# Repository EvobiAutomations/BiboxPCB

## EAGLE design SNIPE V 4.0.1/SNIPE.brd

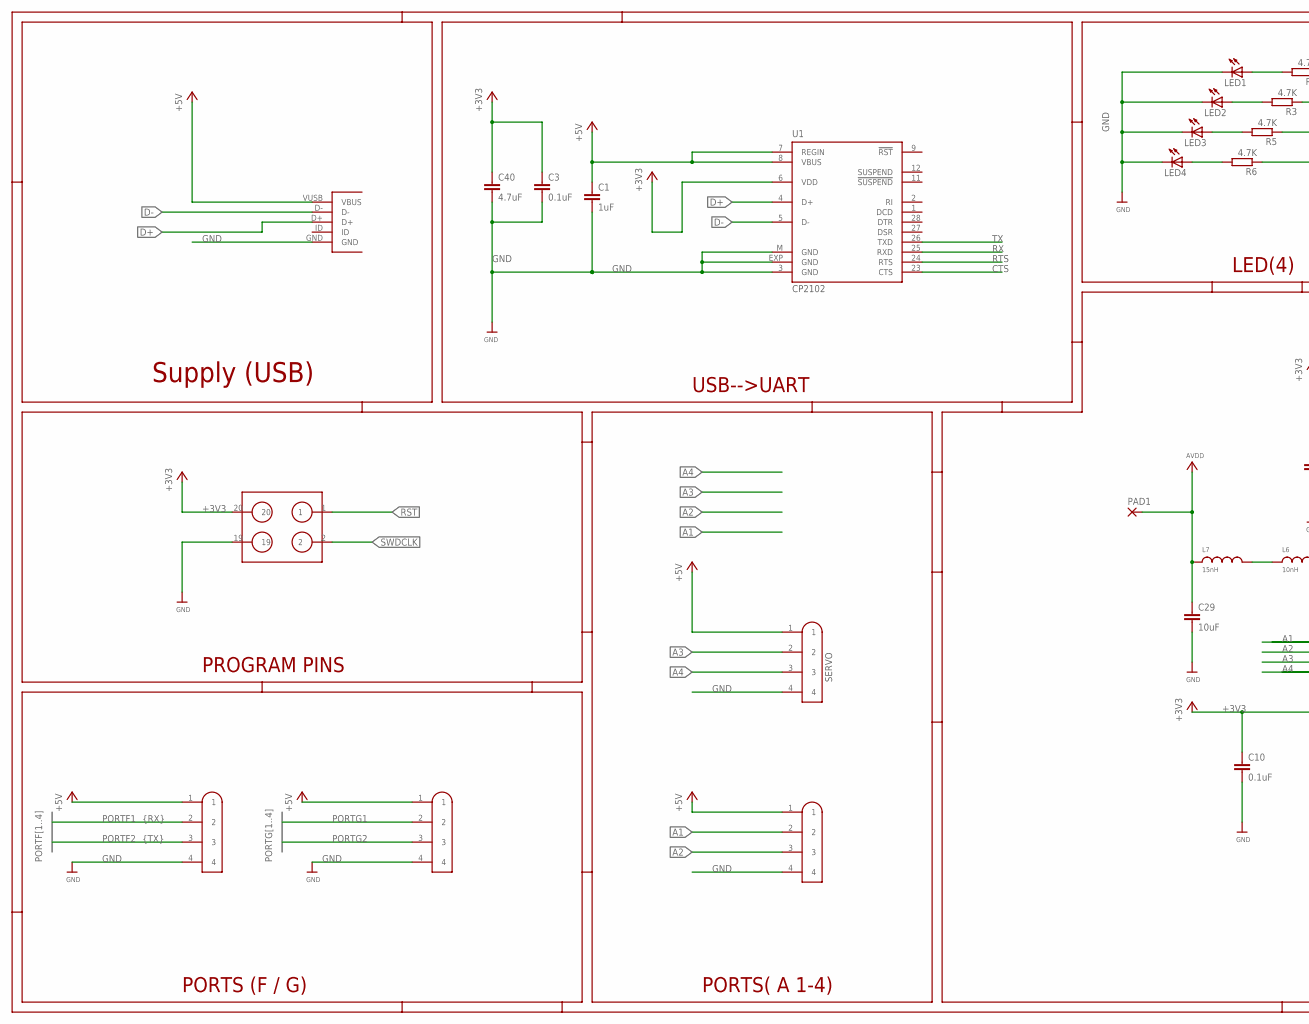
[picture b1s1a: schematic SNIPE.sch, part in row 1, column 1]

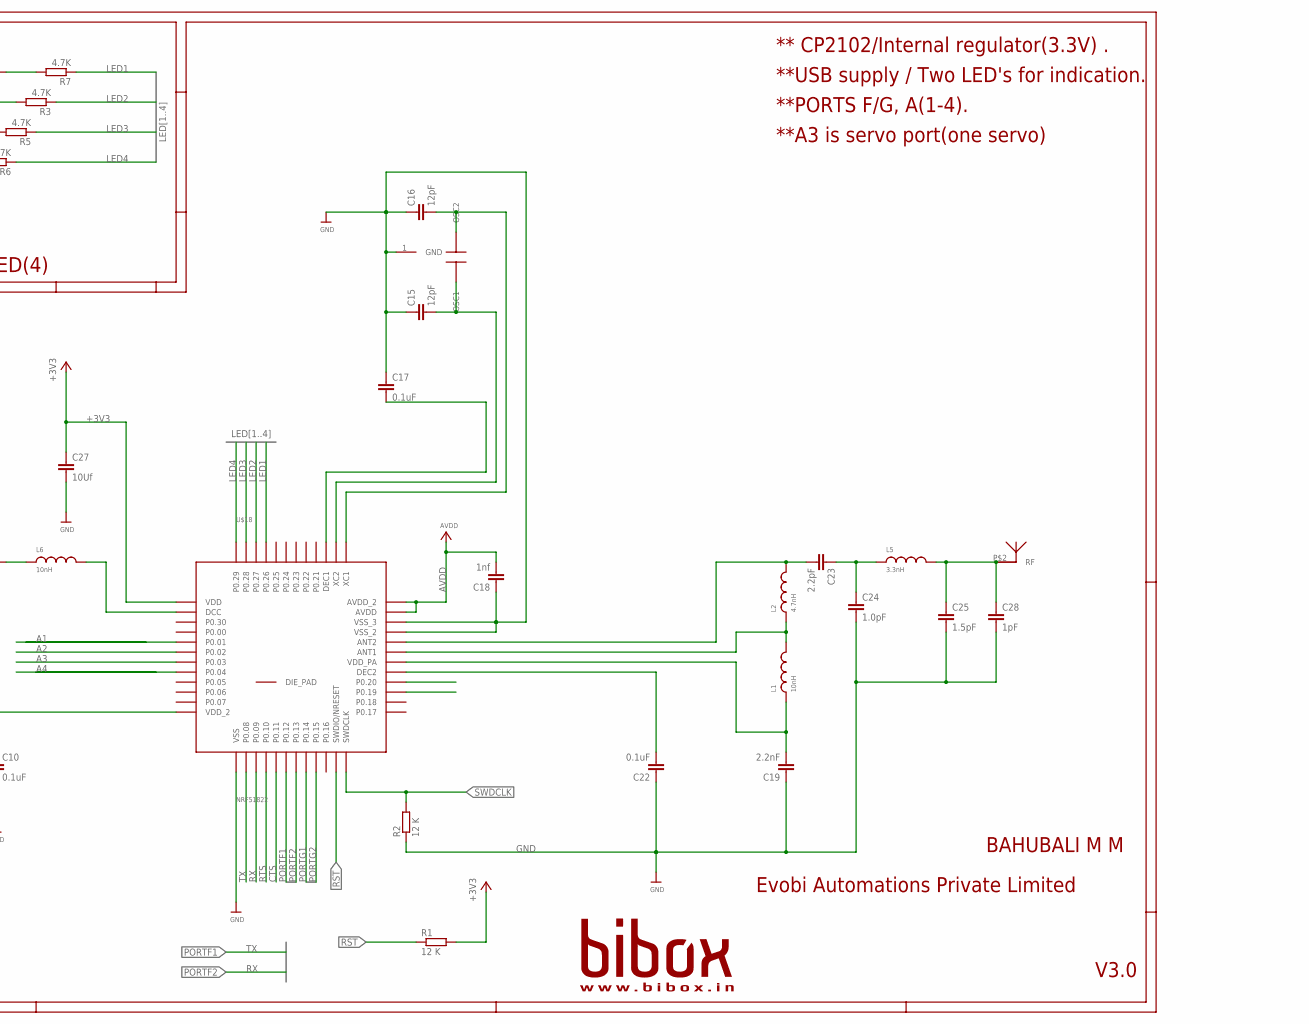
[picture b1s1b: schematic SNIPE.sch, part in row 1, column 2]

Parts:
C1: 1uF; 0603
C3, C10, C17, C22: 0.1uF; C0603
C15, C16: 12pF; C0603
C18: 1nf; C0603
C19: 2.2nF; C0603
C23: 2.2pF; C0603
C24: 1.0pF; C0603
C25: 1.5pF; C0603
C27: 10Uf; C0603
C28: 1pF; C0603
C29: 10uF; C0603
C40: 4.7uF; C0603
L1, L6: 10nH; 0603
L2: 4.7nH; 0603
L5: 3.3nH; 0603
L7: 15nH; 0603
LED1, LED2, LED3, LED4: LEDCHIP-LED0805; CHIP-LED0805
PAD1: SMD2; SMD1,27-2,54
R1, R2: 12 K; R0603
R3, R5, R6, R7: 4.7K; R0603
U1: CP2102; MLP28
U$1: USBMICRO
U$2, U$5, U$19, U$20: 3.5MM-JACK
U$4: CRYSTAL8MHZ; 8MHZ
U$6: 10X2
U$18: NRF51822; QFN48
U$40: WTBT; BTWT

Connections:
+3V3: C3.1, C10.1, C27.1, C40.1, R1.2, U1.6 (VDD), U$6.20, U$18.1 (VDD), U$18.12 (VDD_2)
+5V: C1.1, U1.7 (REGIN), U1.8 (VBUS), U$1.VUSB (VBUS), U$2.1, U$5.1, U$19.1, U$20.1
A1: U$2.2, U$18.5 (P0.01)
A2: U$2.3, U$18.6 (P0.02)
A3: U$5.2, U$18.7 (P0.03)
A4: U$5.3, U$18.8 (P0.04)
AVDD: C18.2, C29.1, L7.1, PAD1.1, U$18.35 (AVDD), U$18.36 (AVDD_2)
CTS: U1.23 (CTS), U$18.17 (P0.11)
D+: U1.4 (D+), U$1.D+
D-: U1.5 (D-), U$1.D-
LED1: R7.1, U$18.45 (P0.26)
LED2: R3.1, U$18.46 (P0.27)
LED3: R5.1, U$18.47 (P0.28)
LED4: R6.1, U$18.48 (P0.29)
unnamed: LED1.A, R7.2
unnamed: LED2.A, R3.2
unnamed: LED3.A, R5.2
unnamed: LED4.A, R6.2
unnamed: C17.2, U$18.39 (DEC1)
unnamed: C16.2, U$4.OSC2, U$18.37 (XC1)
unnamed: C23.2, L2.2, U$18.32 (ANT2)
unnamed: L1.2, L2.1, U$18.31 (ANT1)
unnamed: C23.1, C24.1, L5.1
unnamed: C25.1, C28.1, L5.2, U$40.P$2
unnamed: C19.2, L1.1, U$18.30 (VDD_PA)
unnamed: C15.2, U$4.OSC1, U$18.38 (XC2)
unnamed: C22.2, U$18.29 (DEC2)
unnamed: L6.2, U$18.2 (DCC)
unnamed: L6.1, L7.2
unnamed: C1.2, C3.2, C10.2, C15.1, C16.1, C17.1, C18.1, C19.1, C22.1, C24.2, C25.2, C27.2, C28.2, C29.2, C40.2, LED1.C, LED2.C, LED3.C, LED4.C, R2.1, U1.3 (GND), U1.EXP (GND), U1.M (GND), U$1.GND, U$2.4, U$4.1 (GND), U$5.4, U$6.19, U$18.13 (VSS), U$18.33 (VSS_2), U$18.34 (VSS_3), U$19.4, U$20.4
PORTF1: U$18.18 (P0.12), U$20.2
PORTF2: U$18.19 (P0.13), U$20.3
PORTG1: U$18.20 (P0.14), U$19.2
PORTG2: U$18.21 (P0.15), U$19.3
RST: R1.1, U$6.1, U$18.23 (SWDIO/NRESET)
RTS: U1.24 (RTS), U$18.16 (P0.10)
RX: U1.25 (RXD), U$18.15 (P0.09)
SWDCLK: R2.2, U$6.2, U$18.24 (SWDCLK)
TX: U1.26 (TXD), U$18.14 (P0.08)

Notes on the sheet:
PORTS (F / G)
PROGRAM PINS
Supply (USB)
Evobi Automations Private Limited
BAHUBALI M M
PORTS( A 1-4)
GND
{RX}
{TX}
USB-->UART
V3.0
** CP2102/Internal regulator(3.3V) .
**USB supply / Two LED's for indication.
**PORTS F/G, A(1-4).
**A3 is servo port(one servo)
LED(4)
SERVO

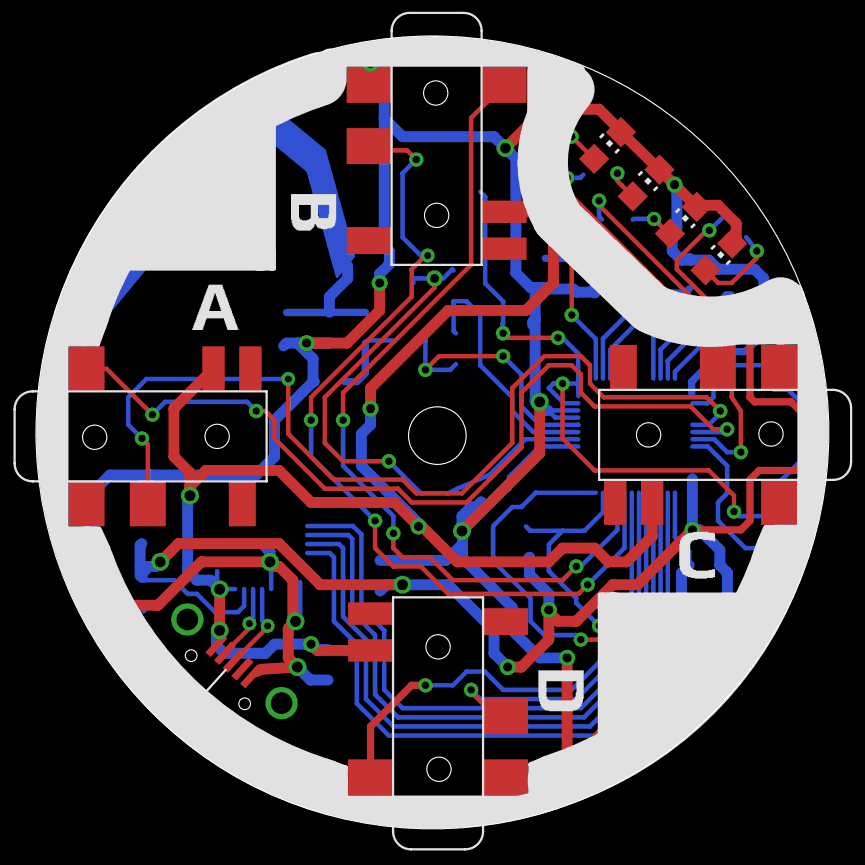
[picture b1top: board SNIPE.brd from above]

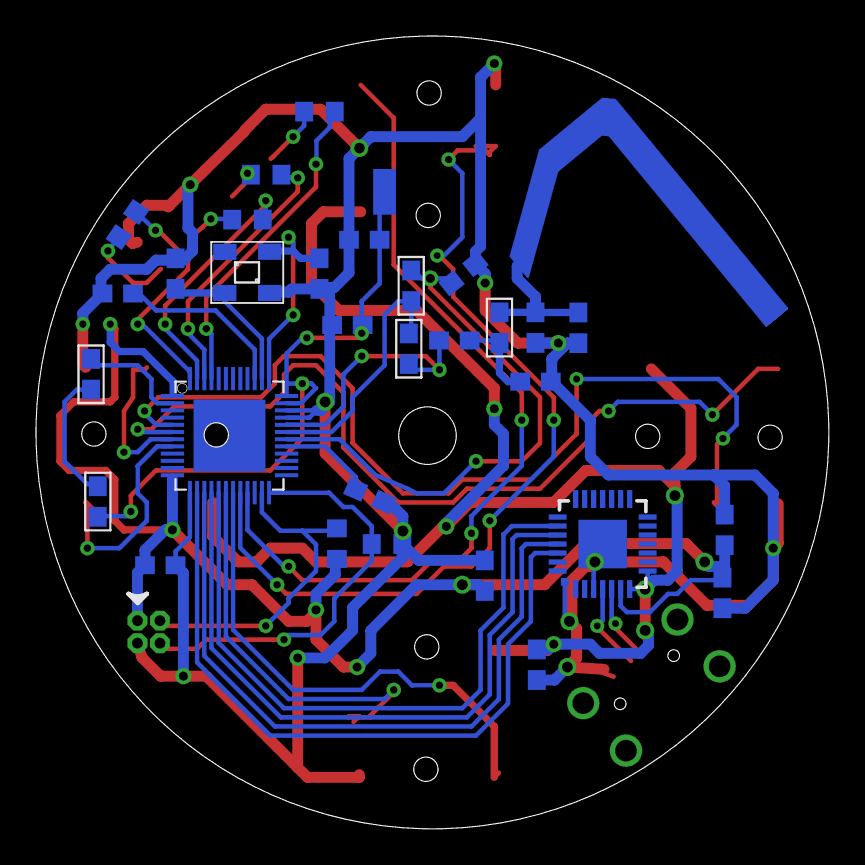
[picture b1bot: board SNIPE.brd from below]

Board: 2 copper layers, 44.0 x 44.0 mm, 42 parts (32 on the bottom side), 39 nets.

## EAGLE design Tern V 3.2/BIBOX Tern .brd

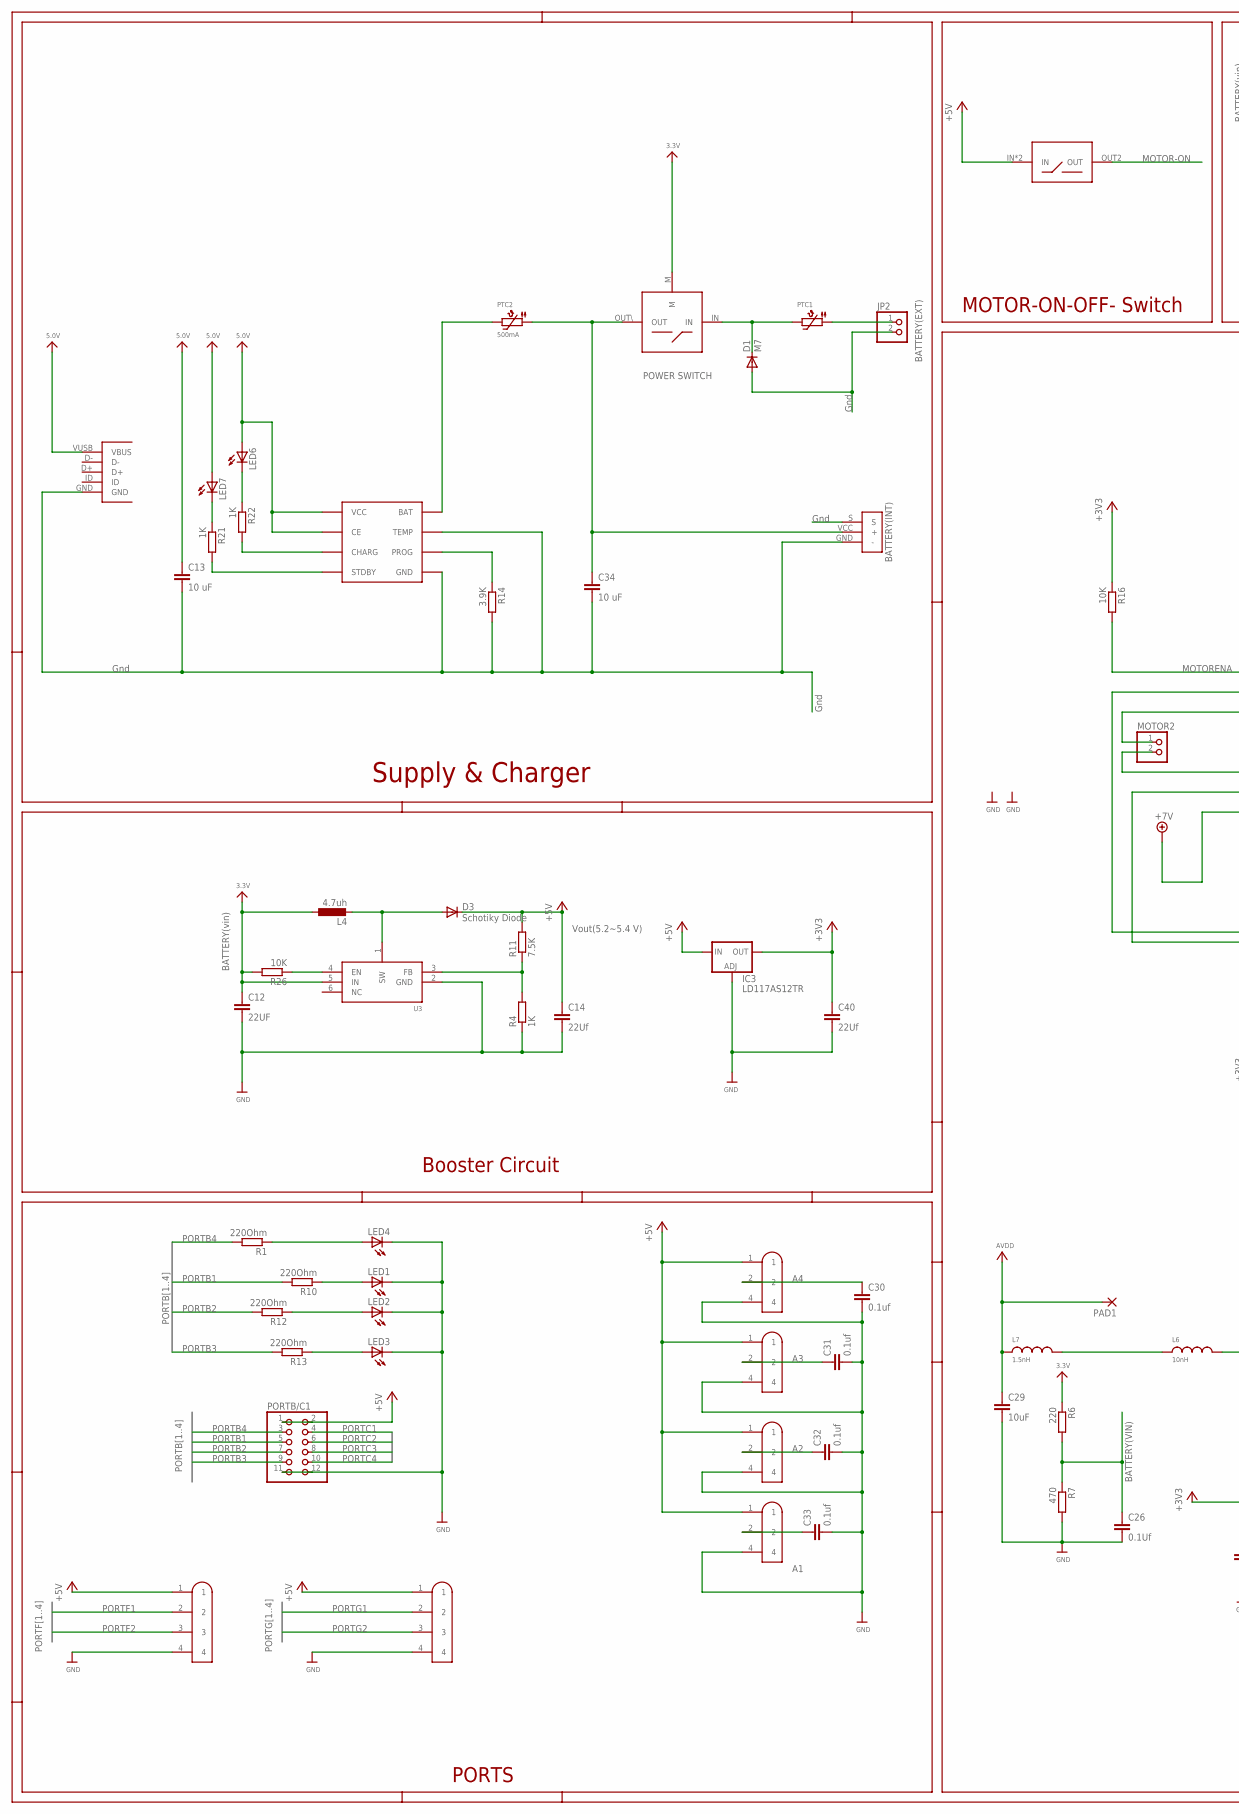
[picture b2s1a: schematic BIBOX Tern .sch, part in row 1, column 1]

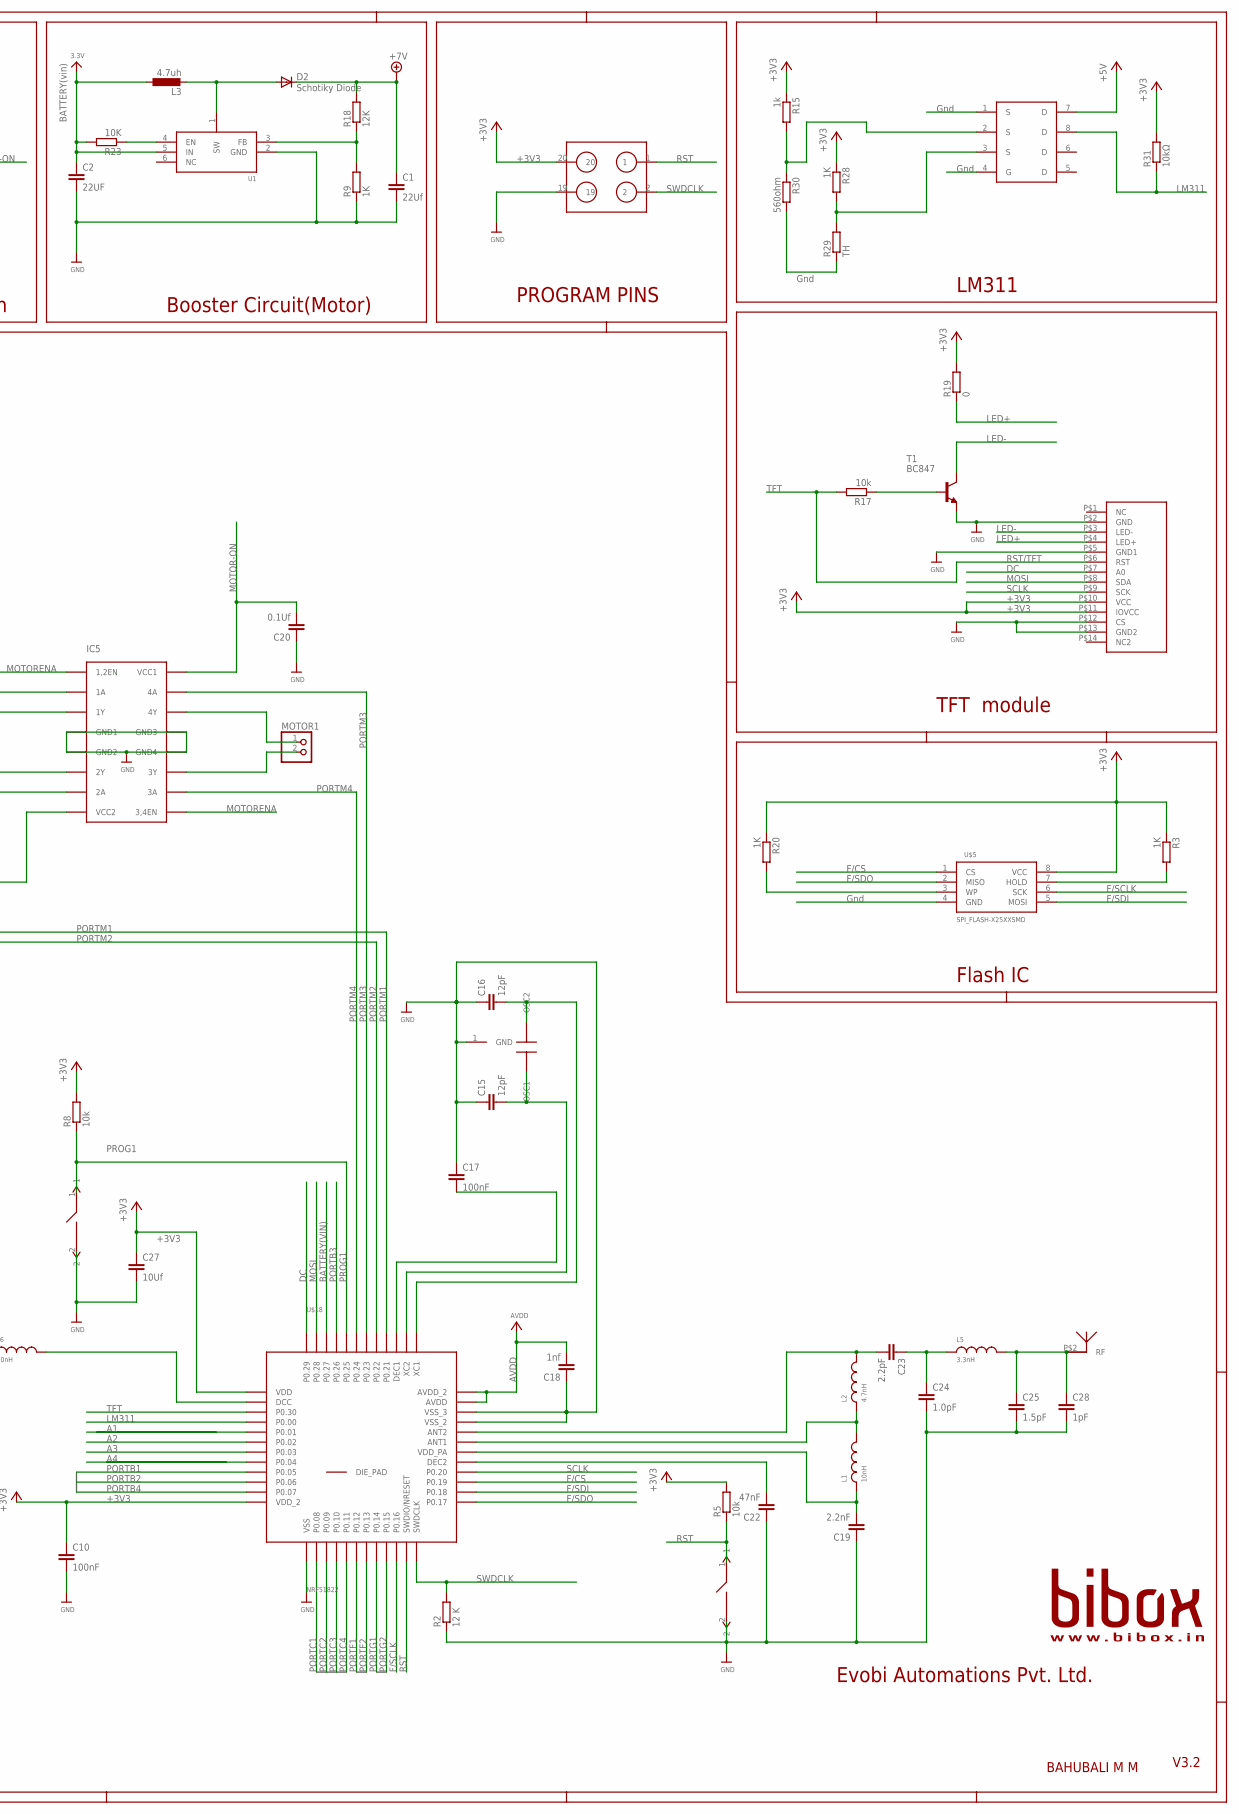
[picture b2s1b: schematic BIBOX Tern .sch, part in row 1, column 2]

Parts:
BATTERY: BS
C1, C14, C40: 22Uf; C0603
C2, C12: 22UF; C0603
C10, C17: 100nF; C0603
C13, C34: 10 uF; C0603
C15, C16: 12pF; C0603
C18: 1nf; C0603
C19: 2.2nF; C0603
C20, C26: 0.1Uf; C0603
C22: 47nF; C0603
C23: 2.2pF; C0603
C24: 1.0pF; C0603
C25: 1.5pF; C0603
C27: 10Uf; C0603
C28: 1pF; C0603
C29: 10uF; C0603
C30, C31, C32, C33: 0.1uf; C0603
D1: M7; SMA-DIODE
D2, D3: Schotiky Diode; SMA-DIODE
IC2: LT1173CS8; SOIC8
IC3: LD117AS12TR; SOT223
IC5: L293D; DIL16
JP2: PINHD-1X2; 1X02
L1, L6: 10nH; 0603
L2: 4.7nH; 0603
L3, L4: 4.7uh; POWER-CHOKE_WE-TPC
L5: 3.3nH; 0603
L7: 1.5nH; 0603
LED1, LED2, LED3, LED4, LED6, LED7: LEDCHIP-LED0805; CHIP-LED0805
MOTOR1, MOTOR2: PINHD-1X2; 1X02
PAD1: SMD2; SMD1,27-2,54
PORTB/C1: PINHD-2X6; 2X06
PTC1: PTC1206; 1206@1
PTC2: 500mA; 1206
R1, R10, R12, R13: 220Ohm; R0603
R2: 12 K; R0603
R3, R4, R9, R20, R21, R22, R28: 1K; R0603
R5, R8, R17: 10k; R0603
R6: 220; R0603
R7: 470; R0603
R11: 7.5K; R0603
R14: 3.9K; R0603
R15: 1k; R0603
R16, R23, R26: 10K; R0603
R18: 12K; R0603
R19: 0; R0603
R29: TH; M1206
R30: 560ohm; R0603
R31: 10kΩ; R0603
RST: NANOSMD\; NANOSMD
T1: BC847; SOT23
U1, U3: MIC5320; SOT23-6
U$1: USBMICRO
U$2: NDS8434; SO08
U$4: CRYSTAL8MHZ; 8MHZ
U$5: SPI_FLASH-X25XXSMD; SO08
U$6: 10X2
U$8: SWITCH; 3PINSWITCH@1
U$9: SWITCH; 3PINSWITCH
U$18: NRF51822; QFN48
U$19, U$20, U$28, U$32, U$34, U$36: 3.5MM-JACK
U$26: LCDDISPLAY1CHAINA; LCDDISPLAY1
U$27: NANOSMD\; NANOSMD
U$40: WTBT; BTWT

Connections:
3.3V: C2.1, C12.1, L3.1, L4.1, R6.1, R23.2, R26.2, U1.5 (IN), U3.5 (IN), U$9.M
5.0V: C13.1, IC2.CE, IC2.VCC, LED6.A, LED7.A, U$1.VUSB (VBUS)
+3V3: C10.1, C27.1, C40.1, IC3.4 (OUT), R3.1, R5.2, R8.2, R15.1, R16.1, R19.2, R20.1, R28.1, R31.2, U$5.8 (VCC), U$6.20, U$18.1 (VDD), U$18.12 (VDD_2), U$26.P$10 (VCC), U$26.P$11 (IOVCC)
+5V: C14.1, D3.C, IC3.3 (IN), PORTB/C1.1, PORTB/C1.2, R11.2, U$2.7 (D), U$8.IN, U$8.OUT1 (IN), U$19.1, U$20.1, U$28.1, U$32.1, U$34.1, U$36.1
+7V: C1.1, D2.C, IC5.8 (VCC2), R18.2
A1: C33.1, U$18.5 (P0.01), U$34.2
A2: C32.1, U$18.6 (P0.02), U$36.2
A3: C31.1, U$18.7 (P0.03), U$32.2
A4: C30.1, U$18.8 (P0.04), U$28.2
AVDD: C18.2, C29.1, L7.1, PAD1.1, U$18.35 (AVDD), U$18.36 (AVDD_2)
BATTERY(VIN): C26.1, R6.2, R7.1, U$18.46 (P0.27)
DC: U$18.48 (P0.29), U$26.P$7 (A0)
F/CS: U$5.1 (CS), U$18.27 (P0.19)
F/SCLK: U$5.6 (SCK), U$18.22 (P0.16)
F/SDI: U$5.5 (MOSI), U$18.26 (P0.18)
F/SDO: U$5.2 (MISO), U$18.25 (P0.17)
LED+: R19.1, U$26.P$4 (LED+)
LED-: T1.3 (C), U$26.P$3 (LED-)
LM311: R31.1, U$2.8 (D), U$18.4 (P0.00)
MOSI: U$18.47 (P0.28), U$26.P$8 (SDA)
MOTOR-ON: C20.2, IC5.16 (VCC1), U$8.OUT2 (OUT)
MOTORENA: IC5.1 (1,2EN), IC5.9 (3,4EN), R16.2
unnamed: R3.2, U$5.7 (HOLD)
unnamed: D2.A, L3.2, U1.1 (SW)
unnamed: JP2.1, PTC1.1
unnamed: R20.2, U$5.3 (WP)
unnamed: C17.2, U$18.39 (DEC1)
unnamed: R9.2, R18.1, U1.3 (FB)
unnamed: R23.1, U1.4 (EN)
unnamed: LED3.A, R13.1
unnamed: LED2.A, R12.1
unnamed: C16.2, U$4.OSC2, U$18.37 (XC1)
unnamed: D3.A, L4.2, U3.1 (SW)
unnamed: LED1.A, R10.1
unnamed: C23.2, L2.2, U$18.32 (ANT2)
unnamed: L1.2, L2.1, U$18.31 (ANT1)
unnamed: R4.2, R11.1, U3.3 (FB)
unnamed: C23.1, C24.1, L5.1
unnamed: C25.1, C28.1, L5.2, U$40.P$2
unnamed: IC5.3 (1Y), MOTOR2.1
unnamed: C19.2, L1.1, U$18.30 (VDD_PA)
unnamed: C15.2, U$4.OSC1, U$18.38 (XC2)
unnamed: C22.2, U$18.29 (DEC2)
unnamed: L6.2, U$18.2 (DCC)
unnamed: L6.1, L7.2
unnamed: IC5.6 (2Y), MOTOR2.2
unnamed: LED4.A, R1.1
unnamed: R17.1, T1.1 (B)
unnamed: IC5.11 (3Y), MOTOR1.2
unnamed: IC5.14 (4Y), MOTOR1.1
unnamed: BATTERY.VCC (+), C34.1, PTC2.1, U$9.OUT\ (OUT)
unnamed: R26.1, U3.4 (EN)
unnamed: BATTERY.GND (-), BATTERY.S, C1.2, C2.2, C10.2, C12.2, C13.2, C14.2, C15.1, C16.1, C17.1, C18.1, C19.1, C20.1, C22.1, C24.2, C25.2, C26.2, C27.2, C28.2, C29.2, C30.2, C31.2, C32.2, C33.2, C34.2, C40.2, D1.A, IC2.GND, IC2.TEMP, IC3.1 (ADJ), IC5.4 (GND1), IC5.5 (GND2), IC5.12 (GND4), IC5.13 (GND3), JP2.2, LED1.C, LED2.C, LED3.C, LED4.C, PORTB/C1.11, PORTB/C1.12, R2.1, R4.1, R7.2, R9.1, R14.2, R29.1, R30.2, RST.2, T1.2 (E), U1.2 (GND), U3.2 (GND), U$1.GND, U$2.1 (S), U$2.4 (G), U$4.1 (GND), U$5.4 (GND), U$6.19, U$18.13 (VSS), U$18.33 (VSS_2), U$18.34 (VSS_3), U$19.4, U$20.4, U$26.P$2 (GND), U$26.P$5 (GND1), U$26.P$12 (CS), U$26.P$13 (GND2), U$27.2, U$28.4, U$32.4, U$34.4, U$36.4
unnamed: R28.2, R29.2, U$2.3 (S)
unnamed: IC2.BAT, PTC2.2
unnamed: R15.2, R30.1, U$2.2 (S)
unnamed: D1.C, PTC1.2, U$9.IN
unnamed: IC2.STDBY, R21.2
unnamed: IC2.PROG, R14.1
unnamed: LED6.C, R22.1
unnamed: IC2.CHRG (CHARG), R22.2
unnamed: LED7.C, R21.1
PORTB1: PORTB/C1.5, R10.2, U$18.9 (P0.05)
PORTB2: PORTB/C1.7, R12.2, U$18.10 (P0.06)
PORTB3: PORTB/C1.9, R13.2, U$18.45 (P0.26)
PORTB4: PORTB/C1.3, R1.2, U$18.11 (P0.07)
PORTC1: PORTB/C1.4, U$18.14 (P0.08)
PORTC2: PORTB/C1.6, U$18.15 (P0.09)
PORTC3: PORTB/C1.8, U$18.16 (P0.10)
PORTC4: PORTB/C1.10, U$18.17 (P0.11)
PORTF1: U$18.18 (P0.12), U$20.2
PORTF2: U$18.19 (P0.13), U$20.3
PORTG1: U$18.20 (P0.14), U$19.2
PORTG2: U$18.21 (P0.15), U$19.3
PORTM1: IC5.2 (1A), U$18.40 (P0.21)
PORTM2: IC5.7 (2A), U$18.41 (P0.22)
PORTM3: IC5.15 (4A), U$18.42 (P0.23)
PORTM4: IC5.10 (3A), U$18.43 (P0.24)
PROG1: R8.1, U$18.44 (P0.25), U$27.1
RST: R5.1, RST.1, U$6.1, U$18.23 (SWDIO/NRESET)
SCLK: U$18.28 (P0.20), U$26.P$9 (SCK)
SWDCLK: R2.2, U$6.2, U$18.24 (SWDCLK)
TFT: R17.2, U$18.3 (P0.30), U$26.P$6 (RST)

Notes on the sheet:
PORTS
PROGRAM PINS
Supply & Charger
TFT module
Booster Circuit
MOTOR-ON-OFF- Switch
Gnd
Flash IC
Booster Circuit(Motor)
BATTERY(INT)
POWER SWITCH
BATTERY(vin)
BATTERY(EXT)
Vout(5.2~5.4 V)
LM311
RST/TFT
BAHUBALI M M
V3.2
Evobi Automations Pvt. Ltd.

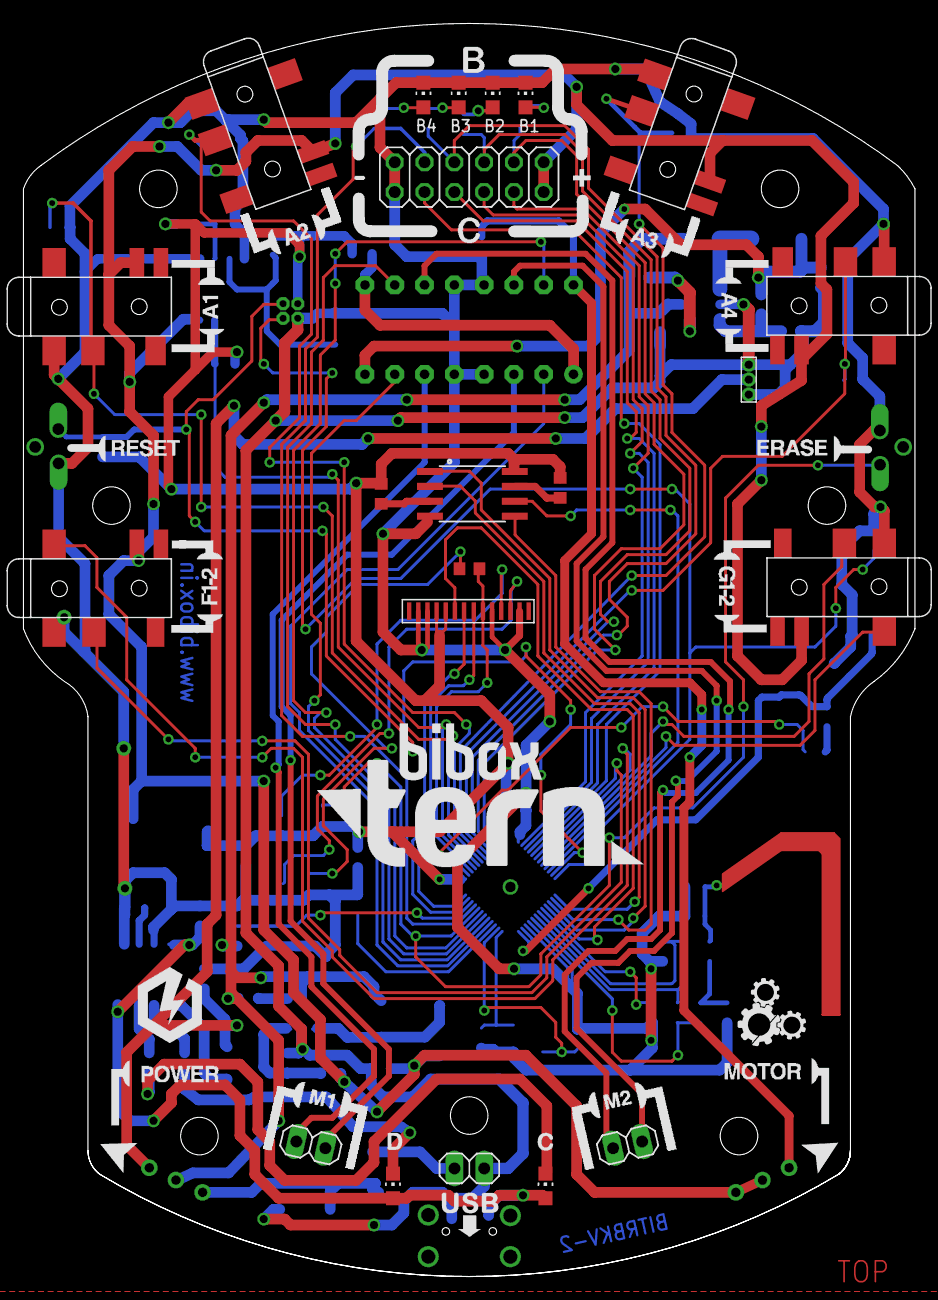
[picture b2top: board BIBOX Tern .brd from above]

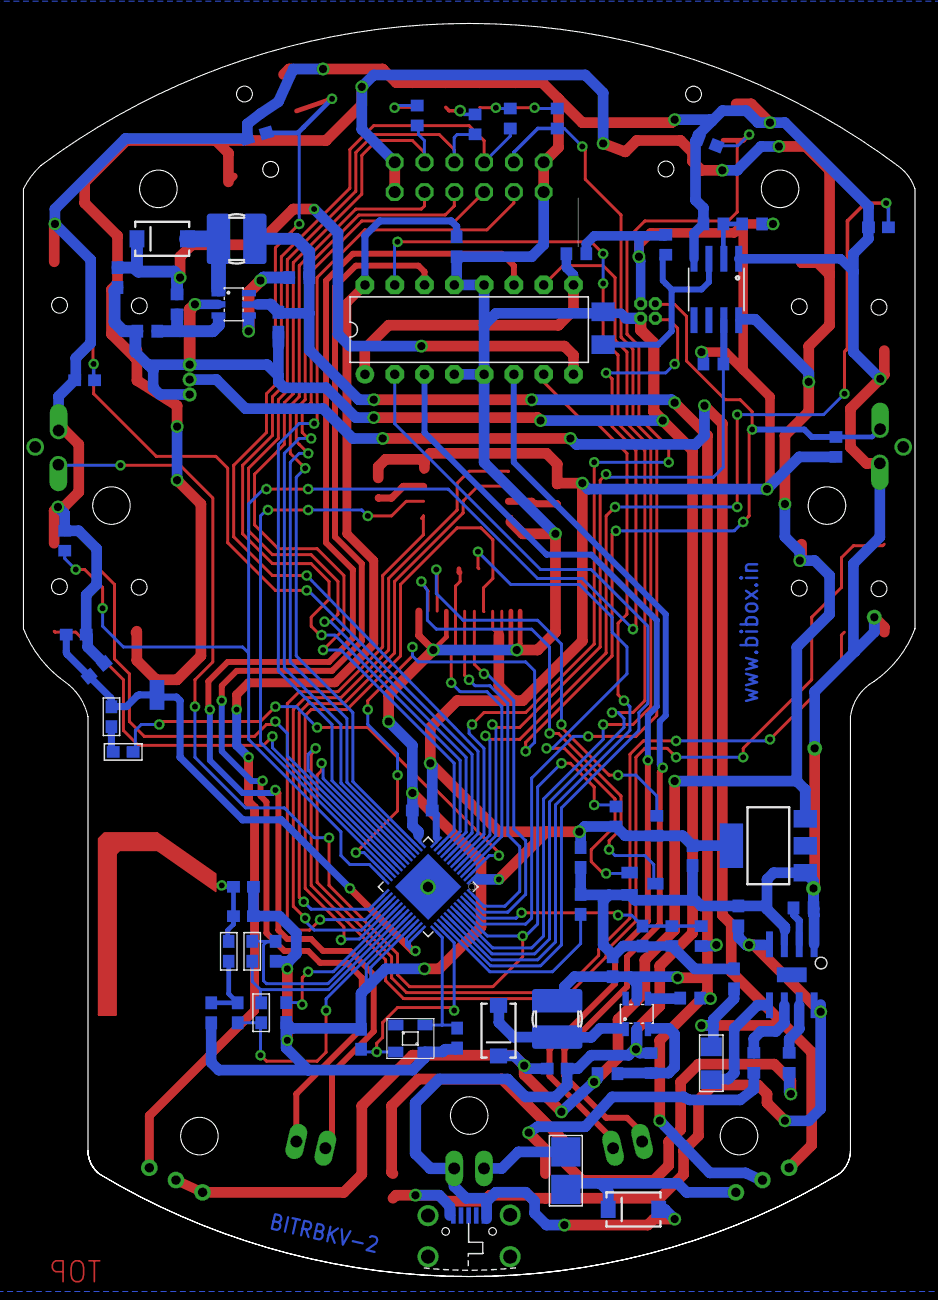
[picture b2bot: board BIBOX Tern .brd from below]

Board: 2 copper layers, 76.0 x 106.8 mm, 102 parts (74 on the bottom side), 83 nets.

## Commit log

2018-08-07 Hornbill pcb files added
2018-08-07 Tern pcb files are added
2018-08-11 Update LICENSE

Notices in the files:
parts and their libraries:
SparkFun: Licensing: CC v3.0 Share-Alike You are welcome to use this library for commercial purposes.
SparkFun-DigitalIC: Licensing: Creative Commons ShareAlike 4.0 International - https://creativecommons.org/licenses/by-sa/4.0
